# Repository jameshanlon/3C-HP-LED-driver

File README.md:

# LED-driver
A three-channel high-power programmable LED driver

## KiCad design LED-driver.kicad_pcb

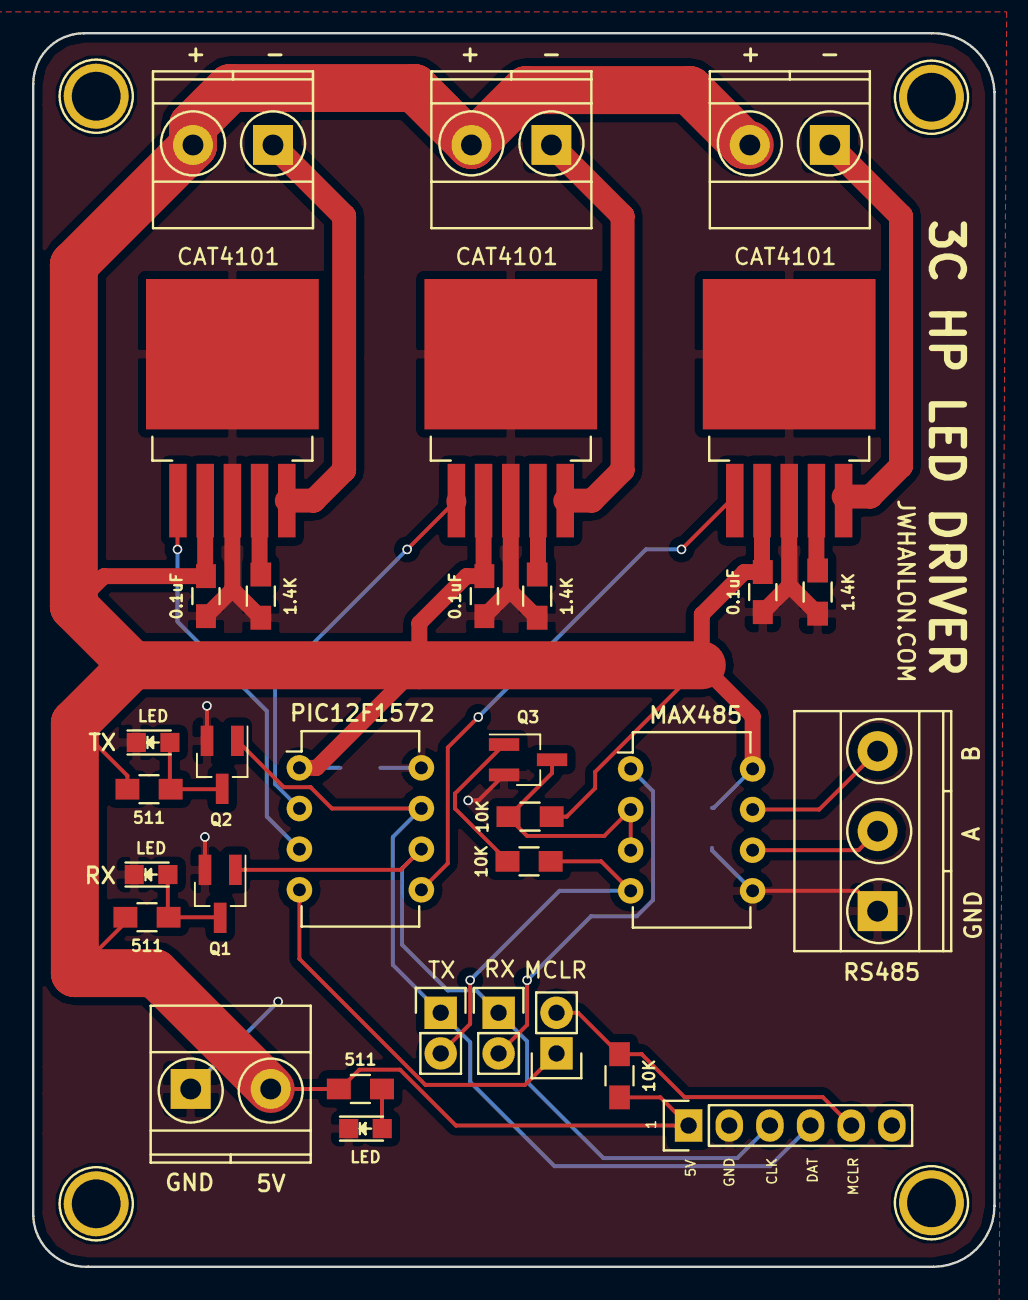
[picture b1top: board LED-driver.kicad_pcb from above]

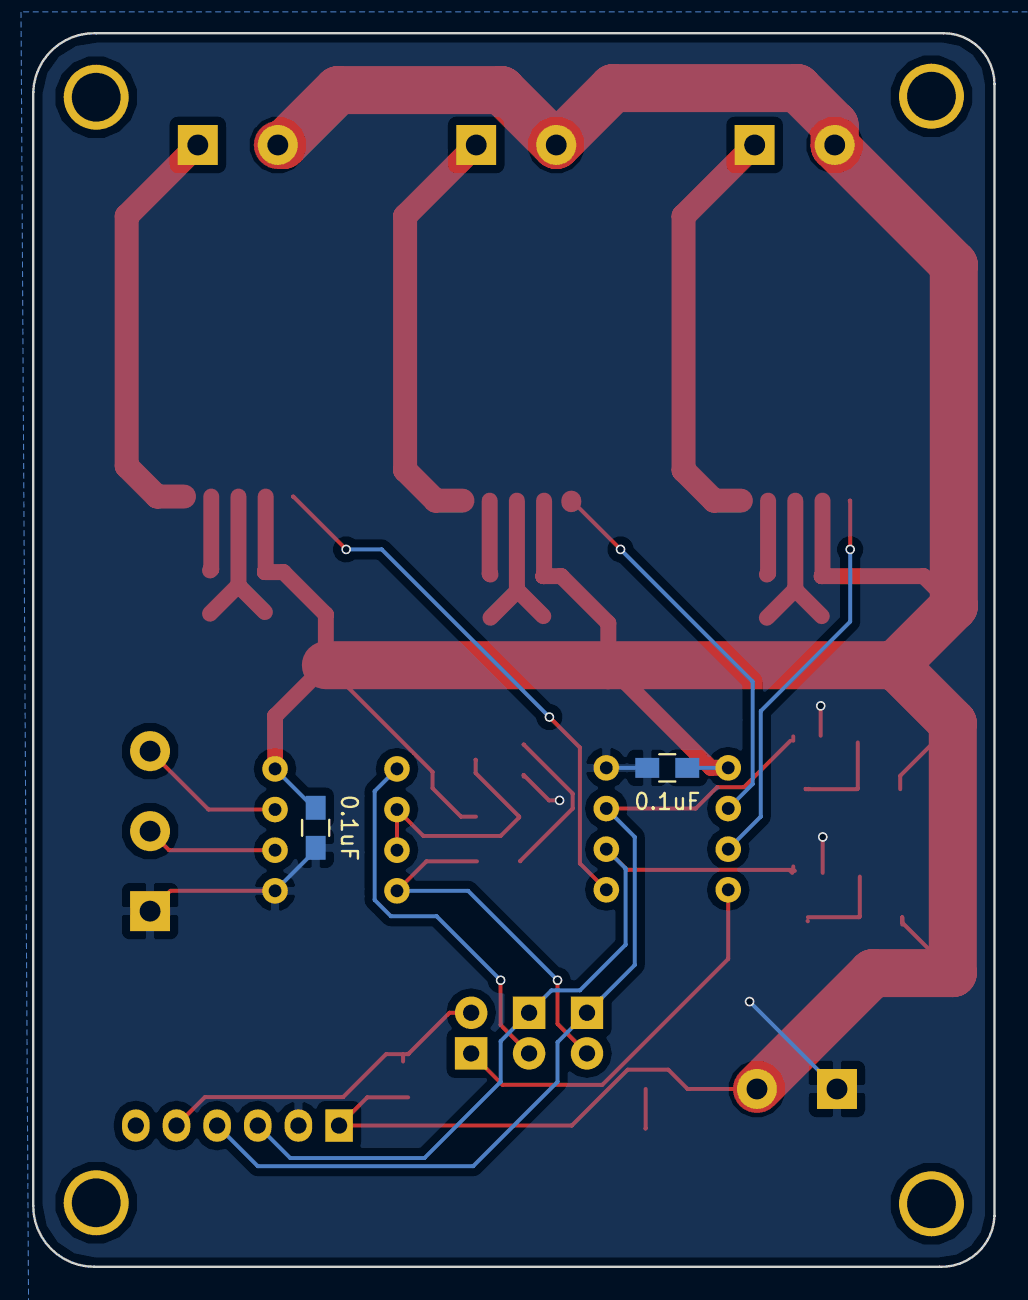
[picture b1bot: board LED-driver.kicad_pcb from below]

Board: 2 copper layers, 60.1 x 77.1 mm, 34 parts (2 on the bottom side), 24 nets.

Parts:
0.1uF1, 0.1uF2, 0.1uF3, 0.1uF4, 0.1uF5: 0.1uF; C_0805_HandSoldering
D1, D2, D3: LED; LED_0805
J1, J3, J4, J5: Screw_Terminal_1x02; TerminalBlock_Pheonix_MKDS1.5-2pol
J2: PIC Kit3 header; Pin_Header_Straight_1x06
J6: Screw_Terminal_1x03; TerminalBlock_Pheonix_MKDS1.5-3pol
JP1: MCLR; Pin_Header_Straight_1x02
JP2: RX; Pin_Header_Straight_1x02
JP3: TX; Pin_Header_Straight_1x02
Q1, Q2, Q3: 2N7002; SOT-23_Handsoldering
R1, R2, R3: 1.4K; R_0805_HandSoldering
R4, R5, R6: 511; R_0805_HandSoldering
R7, R8, R9: 10K; R_0805_HandSoldering
U1: PIC12F1572; DIP-8_W7.62mm
U2, U4, U5: CAT4101; TO-263-5Lead
U3: MAX485; DIP-8_W7.62mm

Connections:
+5V: 0.1uF1.2, 0.1uF2.2, 0.1uF3.2, 0.1uF4.2, 0.1uF5.2, J1.2, J2.1, J3.2, J4.2, J5.2, R4.2, R5.2, R6.1, R7.1, R9.1, U1.1, U2.2, U3.8, U4.2, U5.2
GND: 0.1uF1.1, 0.1uF2.1, 0.1uF3.1, 0.1uF4.1, 0.1uF5.1, D1.1, D2.1, D3.1, J2.2, J5.1, J6.1, Q1.2, Q2.2, Q3.2, R1.2, R2.2, R3.2, U1.8, U2.3, U3.5, U4.3, U5.3
MCLR: JP1.1, U1.4
unnamed: D1.2, Q1.3, R4.1
unnamed: D2.2, R6.2
unnamed: D3.2, Q2.3, R5.1
unnamed: J1.1, U2.5
unnamed: J2.5, JP1.2, R7.2
unnamed: J3.1, U4.5
unnamed: J4.1, U5.5
unnamed: J6.2, U3.6
unnamed: J6.3, U3.7
unnamed: JP2.2, U3.1
unnamed: JP3.2, R8.2, U3.4
unnamed: Q3.1, R8.1
unnamed: Q3.3, R9.2, U3.2, U3.3
unnamed: R1.1, U2.4
unnamed: R2.1, U4.4
unnamed: R3.1, U5.4
unnamed: U1.2, U4.1
unnamed: U1.3, U5.1
unnamed: U1.5, U2.1
UART_RX/CLK: J2.3, JP2.1, Q1.1, U1.6
UART_TX/DAT: J2.4, JP3.1, Q2.1, U1.7

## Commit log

2017-08-21 Initial commit of files.
2017-08-21 Various tweaks and Gerber export.
2017-08-22 Update schematic and netlist.
2017-08-23 Fix schematic-PCB references and update GBR files.
2017-08-27 Tweaks to vias.
2017-08-27 Tweak resistor values.
2017-09-03 Final tweaks.
2017-09-20 Fix pins of FETs and other board tweaks.
2017-09-24 Final tweaks for version 2.
2018-01-24 Add PIC12F572 source code and MPLab project
2018-01-24 Move PCB files to separate directory
2018-03-18 MPLab project files update
